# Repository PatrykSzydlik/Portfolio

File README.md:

# Portfolio
Projekty nad którymi pracowałem oraz przykłady kodu napisanego prywatnie lub na potrzeby studiów

1. Projekt Ariadna  - robot saperski z napędem gąsienicowym, rozwijany w ramach działalności w kole naukowym KNR KoNaR - folder zawiera wyrenderowany podgląd konstrukcji robota, jego rzeczywisty wygląd oraz zdjęcia wyszczególnionych części, które zaprojektowałem na potrzeby napędu

2. Projekt MegaZord - robot turniejowy klasy Linefollower, który został od podstaw zaprojektowany i zbudowany przeze mnie - folder zawiera kod wraz z konfiguracją STM32CubeIDE, zrzuty ekranu schematu elektronicznego oraz projektu płytki PCB oraz prezentacje dotyczące kontruskcji wykonane na potrzeby studiów

3. Algorytmy i Metody Sztucznej Inteligencji - kurs z programowania, w którym zaimplementowałem dane algorytmy i struktury wykorzystując obiektowe podejście języka C++ - folder zawiera mój kod oraz sprawozdania wykonane podczas kursu

4. Programowanie obiektowe - kurs programowania z wykorzystaniem obiektowego podejścia języka C++ - folder zawiera kod, napisany w ramach zajęć, którego zadaniem była symulacja i kontrolowanie modelu poruszającego się drona z wykorzystaniem bibliotek do obsługi programu GPlot

5. Podstawy programowania - kurs podstaw programowania w języku C - folder zawiera przykładowe aplikacje napisane w C, najbardziej rozbudowana z nich służy do obróbki zdjęć w podstawowych formatach

6. Modele CAD figurek czołgów - moje pierwsze modele wykonane hobbystycznie z czasów licealnych, gdy dopiero poznawałem możliwości programów typu CAD - folder zawiera głównie zdjęcia przedstawiające poszczególne modele

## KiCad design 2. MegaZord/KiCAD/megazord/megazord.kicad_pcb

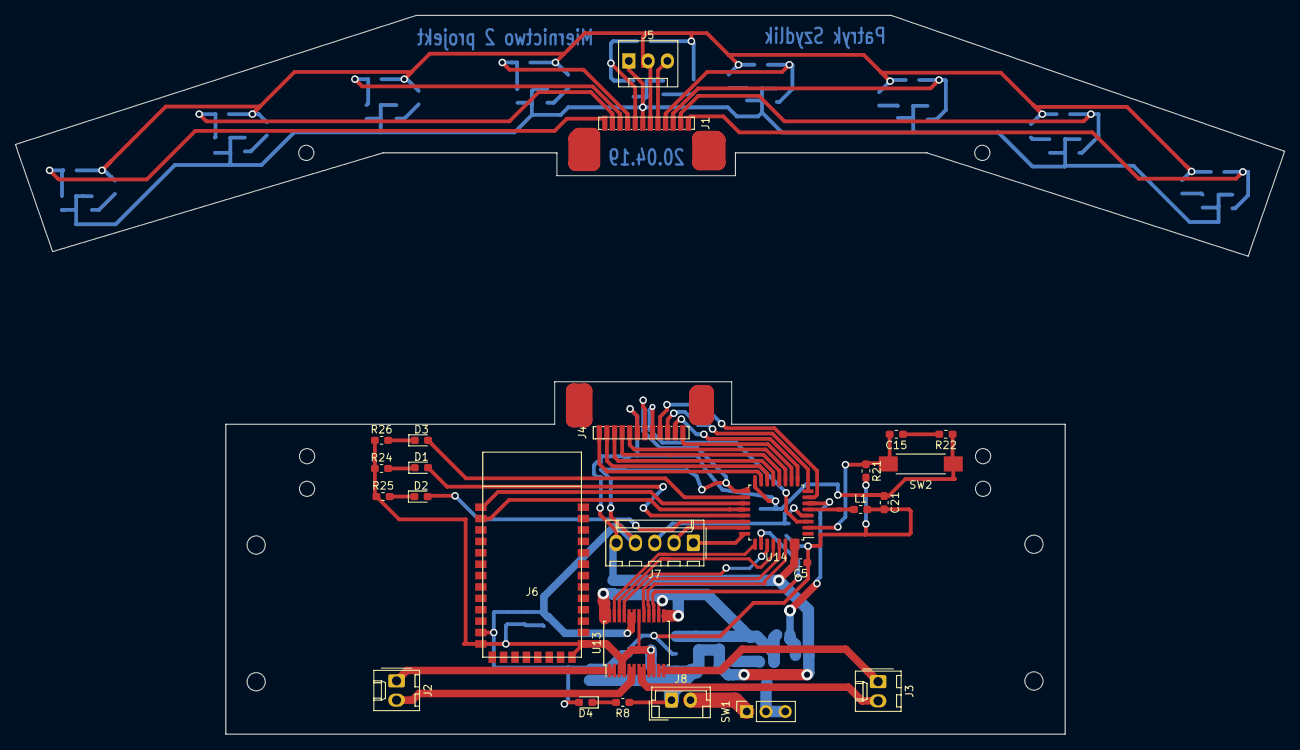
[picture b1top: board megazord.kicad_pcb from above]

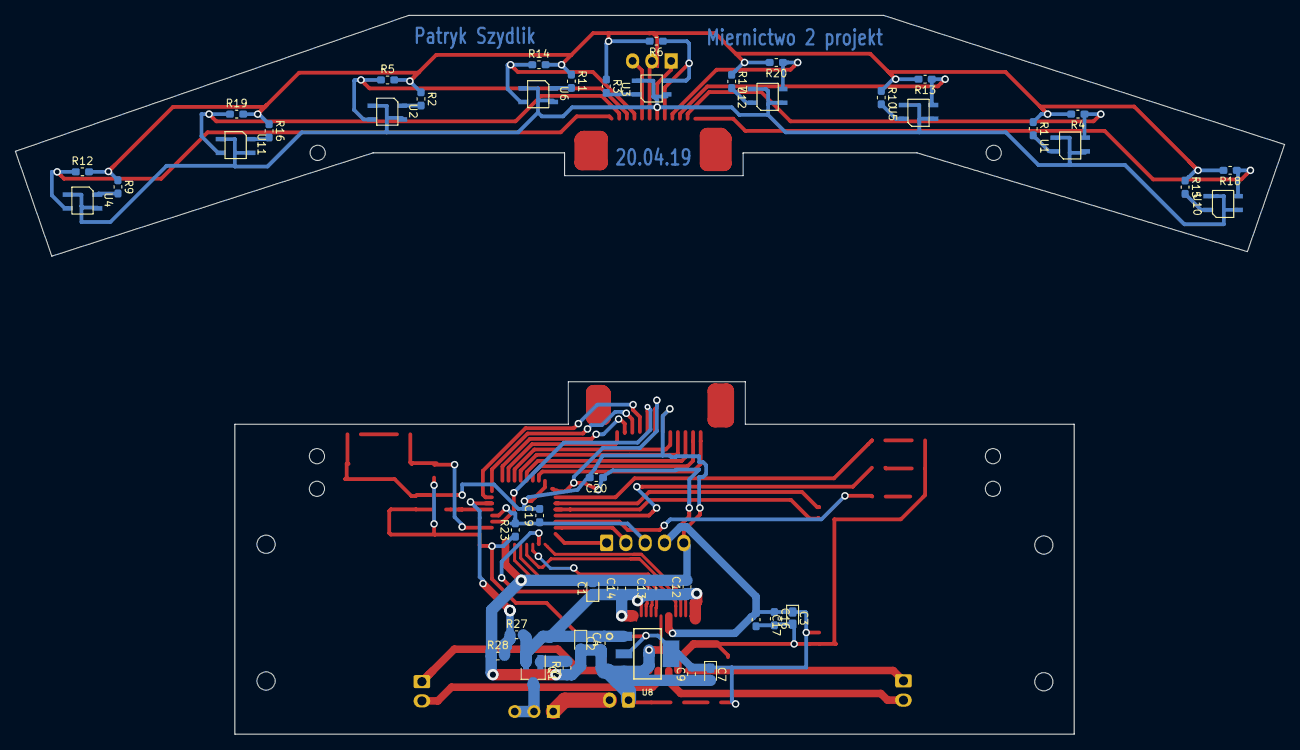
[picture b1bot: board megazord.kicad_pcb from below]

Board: 2 copper layers, 167.1 x 94.6 mm, 72 parts (46 on the bottom side), 21 nets.

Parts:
C1, C3, C4, C7: 10uF; CP_EIA-1608-08_AVX-J_Pad1.25x1.05mm_HandSolder
C2, C5, C9, C12, C13, C14, C15, C16, C17, C19, C20, C21: 100nF; C_0603_1608Metric_Pad1.05x0.95mm_HandSolder
D1: RED; LED_0603_1608Metric_Pad1.05x0.95mm_HandSolder
D2: ORANGE; LED_0603_1608Metric_Pad1.05x0.95mm_HandSolder
D3: BLUE; LED_0603_1608Metric_Pad1.05x0.95mm_HandSolder
D4: GREEN; LED_0603_1608Metric_Pad1.05x0.95mm_HandSolder
J1, J4: Conn_01x12; PinSocket_1x12_P1.00mm_Vertical_SMD
J2, J3: Conn_01x02; Molex_KK-254_AE-6410-02A_1x02_P2.54mm_Vertical
J5: CZ_OD; FanPinHeader_1x03_P2.54mm_Vertical
J6: BLUETOOTH; HC-06
J7: PROGRAMATOR; Molex_KK-254_AE-6410-05A_1x05_P2.54mm_Vertical
J8: Conn_01x02; JST_EH_B2B-EH-A_1x02_P2.50mm_Vertical
L1: 10uH; L_0603_1608Metric_Pad1.05x0.95mm_HandSolder
Q1: Q_PMOS_GSD; SOT-23_Handsoldering
R1, R2, R3, R9, R10, R11, R15, R16, R17, R22: 220; R_0603_1608Metric_Pad1.05x0.95mm_HandSolder
R4, R5, R6, R12, R13, R14, R18, R19, R20: 10k; R_0603_1608Metric_Pad1.05x0.95mm_HandSolder
R7: 1.5k; R_0603_1608Metric_Pad1.05x0.95mm_HandSolder
R8, R24, R25, R26: 330; R_0603_1608Metric_Pad1.05x0.95mm_HandSolder
R21: 4k7; R_0603_1608Metric_Pad1.05x0.95mm_HandSolder
R23, R27: 100k; R_0603_1608Metric_Pad1.05x0.95mm_HandSolder
R28: 47k; R_0603_1608Metric_Pad1.05x0.95mm_HandSolder
SW1: ON/OFF; PinSocket_1x03_P2.54mm_Vertical
SW2: SWITCH; SW_SPST_REED_CT05-XXXX-G1
U1, U2, U3, U4, U5, U6, U10, U11, U12: KTIR0711S
U8: LM1117-3.3; LM1117_SOT223
U13: TB6612
U14: STM32L071KBTx; LQFP-32_7x7mm_P0.8mm

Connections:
+3V3: J1.6, J5.2, R1.1, R2.1, R3.1, R4.2, R5.2, R6.2, R9.1, R10.1, R11.1, R12.2, R13.2, R14.2, R15.1, R16.1, R17.1, R18.2, R19.2, R20.2
CZ_0: J1.8, R6.1, U3.4
CZ_1: J1.4, R14.1, U6.4
CZ_2: J1.9, R20.1, U12.4
CZ_3: J1.3, R5.1, U2.4
CZ_4: J1.10, R13.1, U5.4
CZ_5: J1.2, R19.1, U11.4
CZ_6: J1.11, R4.1, U1.4
CZ_7: J1.1, R12.1, U4.4
CZ_8: J1.12, R18.1, U10.4
CZ_OD: J1.5, J5.3
GND: J1.7, J5.1, U1.2, U1.3, U2.2, U2.3, U3.2, U3.3, U4.2, U4.3, U5.2, U5.3, U6.2, U6.3, U10.2, U10.3, U11.2, U11.3, U12.2, U12.3
unnamed: R1.2, U1.1
unnamed: R2.2, U2.1
unnamed: R3.2, U3.1
unnamed: R9.2, U4.1
unnamed: R10.2, U5.1
unnamed: R11.2, U6.1
unnamed: R15.2, U10.1
unnamed: R16.2, U11.1
unnamed: R17.2, U12.1

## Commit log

2020-06-25 Included CAD models in part 1 and 6. Included sources for part 2.
2020-06-26 Included programming projects and presentation for MegaZord
2020-06-26 Included programming projects
